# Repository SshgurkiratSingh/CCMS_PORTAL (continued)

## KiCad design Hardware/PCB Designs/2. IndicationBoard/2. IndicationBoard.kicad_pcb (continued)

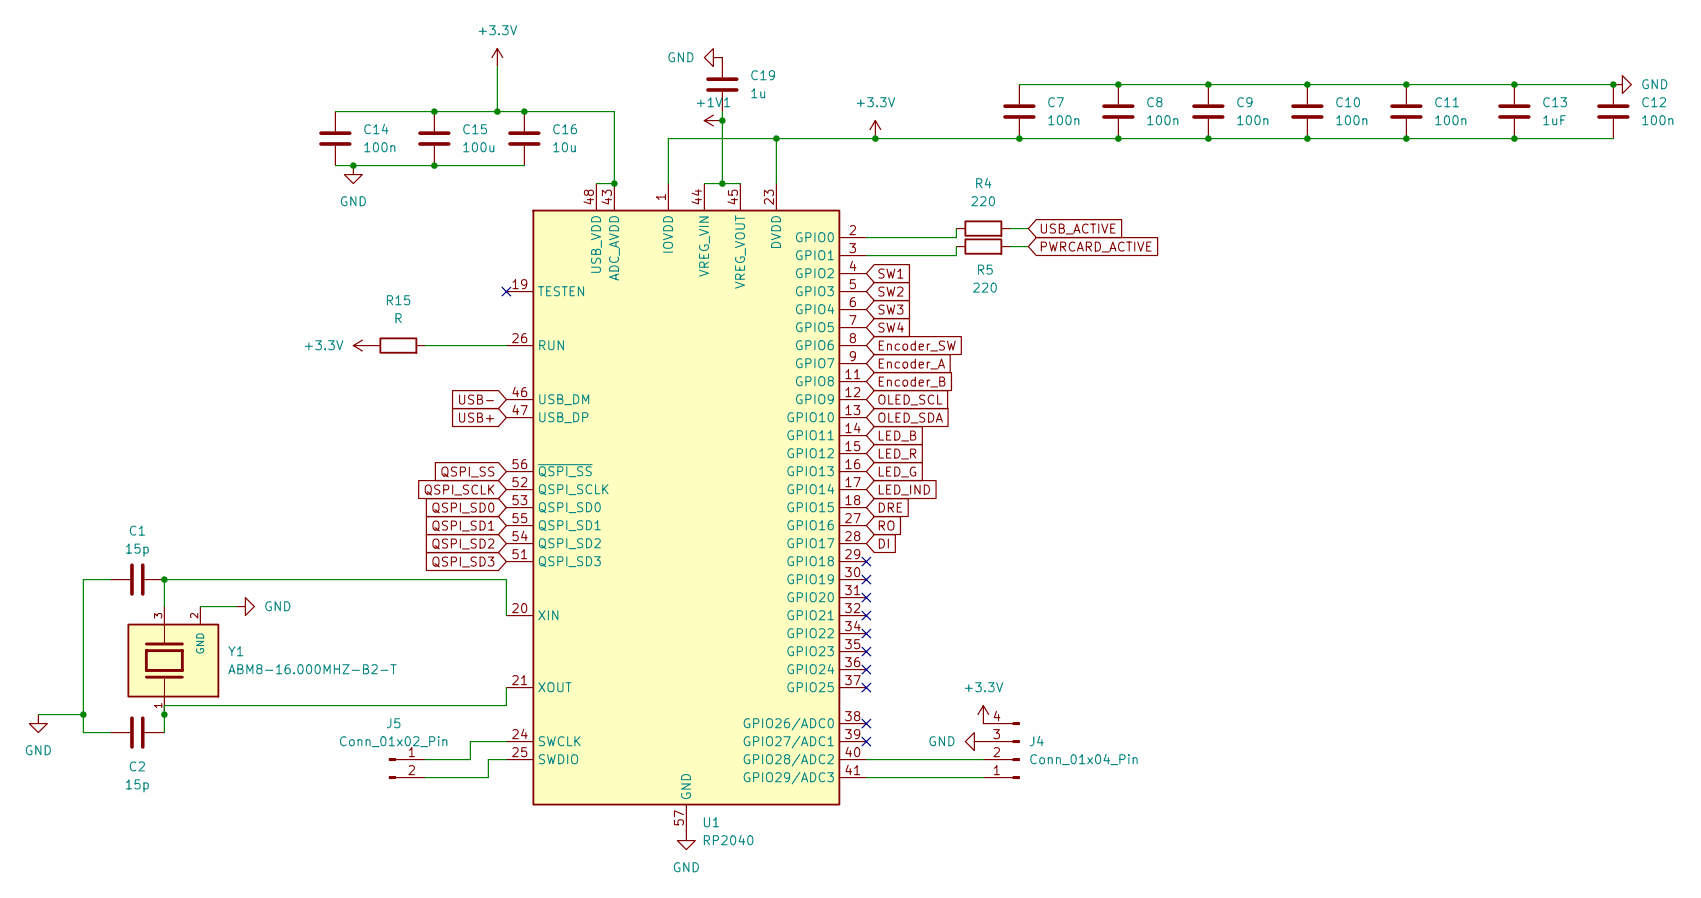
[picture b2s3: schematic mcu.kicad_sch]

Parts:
C1, C2: 15p; C_0402_1005Metric
C7, C8, C9, C10, C11, C12, C14: 100n; C_0201_0603Metric
C13: 1uF; C_0201_0603Metric
C15: 100u; C_0201_0603Metric
C16: 10u; C_0201_0603Metric
C19: 1u; C_0201_0603Metric
J4: Conn_01x04_Pin; PinSocket_1x04_P1.00mm_Vertical
J5: Conn_01x02_Pin; PinSocket_1x02_P2.00mm_Vertical
R4, R5: 220; R_0402_1005Metric
R15: R; R_0201_0603Metric
U1: RP2040; QFN-56-1EP_7x7mm_P0.4mm_EP3.2x3.2mm
Y1: ABM8-16.000MHZ-B2-T; XTAL_ABM8-16.000MHZ-B2-T; PARTREV 44041

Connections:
+1V1: C19.2, U1.44 (VREG_VIN), U1.45 (VREG_VOUT); also elsewhere on the board
+3.3V: C7.2, C8.2, C9.2, C10.2, C11.2, C12.2, C13.2, C14.1, C15.1, C16.1, J4.4, R15.1, U1.1 (IOVDD), U1.10 (IOVDD), U1.22 (IOVDD), U1.23 (DVDD), U1.33 (IOVDD), U1.42 (IOVDD), U1.43 (ADC_AVDD), U1.48 (USB_VDD), U1.49 (IOVDD), U1.50 (DVDD); also elsewhere on the board
DI: U1.28 (GPIO17); also elsewhere on the board
DRE: U1.18 (GPIO15); also elsewhere on the board
Encoder_A: U1.9 (GPIO7); also elsewhere on the board
Encoder_B: U1.11 (GPIO8); also elsewhere on the board
Encoder_SW: U1.8 (GPIO6); also elsewhere on the board
GND: C1.1, C2.1, C7.1, C8.1, C9.1, C10.1, C11.1, C12.1, C13.1, C14.2, C15.2, C16.2, C19.1, J4.3, U1.57 (GND), Y1.2 (GND), Y1.4 (GND); also elsewhere on the board
LED_B: U1.14 (GPIO11); also elsewhere on the board
LED_G: U1.16 (GPIO13); also elsewhere on the board
LED_IND: U1.17 (GPIO14); also elsewhere on the board
LED_R: U1.15 (GPIO12); also elsewhere on the board
unnamed: J4.1, U1.41 (GPIO29/ADC3)
unnamed: J4.2, U1.40 (GPIO28/ADC2)
unnamed: J5.1, U1.24 (SWCLK)
unnamed: J5.2, U1.25 (SWDIO)
unnamed: R4.1, U1.2 (GPIO0)
unnamed: R5.1, U1.3 (GPIO1)
unnamed: R15.2, U1.26 (RUN)
unnamed: C1.2, U1.20 (XIN), Y1.3
unnamed: C2.2, U1.21 (XOUT), Y1.1
OLED_SCL: U1.12 (GPIO9); also elsewhere on the board
OLED_SDA: U1.13 (GPIO10); also elsewhere on the board
PWRCARD_ACTIVE: R5.2; also elsewhere on the board
QSPI_SCLK: U1.52 (QSPI_SCLK); also elsewhere on the board
QSPI_SD0: U1.53 (QSPI_SD0); also elsewhere on the board
QSPI_SD1: U1.55 (QSPI_SD1); also elsewhere on the board
QSPI_SD2: U1.54 (QSPI_SD2); also elsewhere on the board
QSPI_SD3: U1.51 (QSPI_SD3); also elsewhere on the board
QSPI_SS: U1.56 (~QSPI_SS); also elsewhere on the board
RO: U1.27 (GPIO16); also elsewhere on the board
SW1: U1.4 (GPIO2); also elsewhere on the board
SW2: U1.5 (GPIO3); also elsewhere on the board
SW3: U1.6 (GPIO4); also elsewhere on the board
SW4: U1.7 (GPIO5); also elsewhere on the board
USB+: U1.47 (USB_DP); also elsewhere on the board
USB-: U1.46 (USB_DM); also elsewhere on the board
USB_ACTIVE: R4.2; also elsewhere on the board

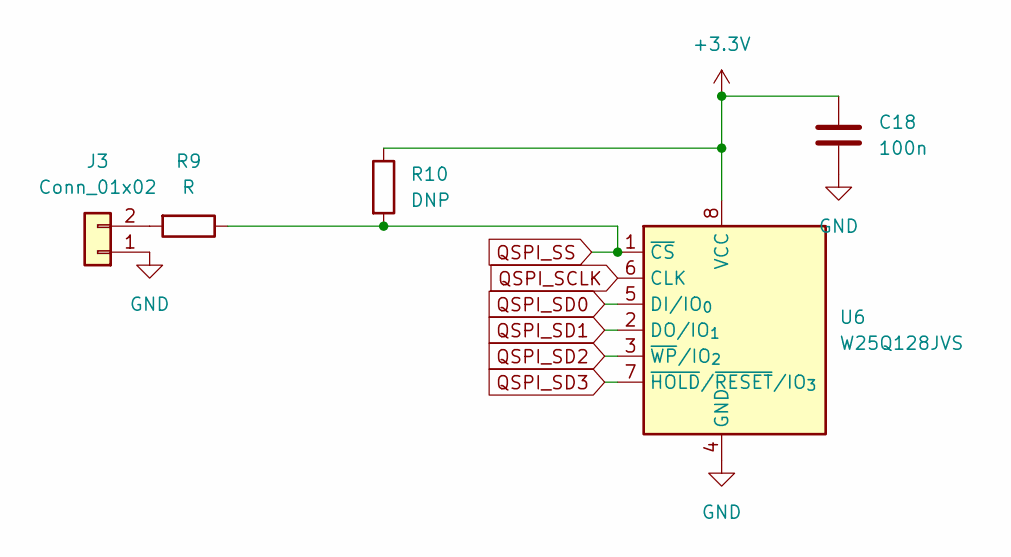
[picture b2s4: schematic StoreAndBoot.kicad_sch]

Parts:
C18: 100n; C_0402_1005Metric
J3: Conn_01x02; PinHeader_1x02_P1.00mm_Vertical
R9: R; R_0402_1005Metric
R10: DNP; R_0805_2012Metric
U6: W25Q128JVS; SOIC-8_5.3x5.3mm_P1.27mm

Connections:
+3.3V: C18.1, R10.1, U6.8 (VCC); also elsewhere on the board
GND: C18.2, J3.1, U6.4 (GND); also elsewhere on the board
unnamed: J3.2, R9.2
QSPI_SCLK: U6.6 (CLK); also elsewhere on the board
QSPI_SD0: U6.5 (DI/IO_{0}); also elsewhere on the board
QSPI_SD1: U6.2 (DO/IO_{1}); also elsewhere on the board
QSPI_SD2: U6.3 (~WP/IO_{2}); also elsewhere on the board
QSPI_SD3: U6.7 (~HOLD/~RESET/IO_{3}); also elsewhere on the board
QSPI_SS: R9.1, R10.2, U6.1 (~CS); also elsewhere on the board

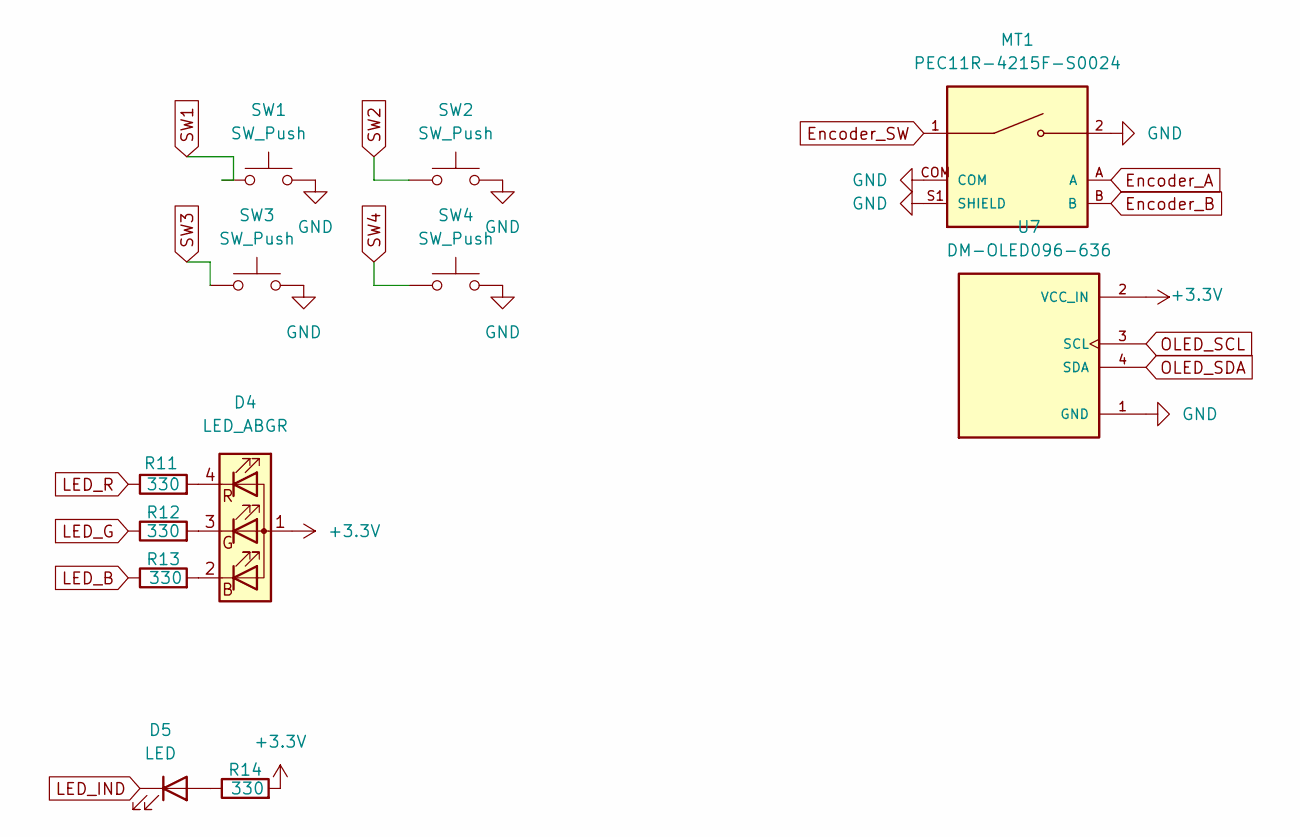
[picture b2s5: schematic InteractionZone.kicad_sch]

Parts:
D4: LED_ABGR; LED_RGB_Wuerth-PLCC4_3.2x2.8mm_150141M173100
D5: LED; LED_0805_2012Metric
MT1: PEC11R-4215F-S0024; XDCR_PEC11R-4215F-S0024; PARTREV Rev. 09/19
R11, R12, R13, R14: 330; R_0201_0603Metric
SW1, SW2, SW3, SW4: SW_Push; SW_PUSH_6mm_H8mm
U7: DM-OLED096-636; MODULE_DM-OLED096-636; PARTREV 2018-09-10

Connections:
+3.3V: D4.1 (A), R14.2, U7.2 (VCC_IN); also elsewhere on the board
Encoder_A: MT1.A; also elsewhere on the board
Encoder_B: MT1.B; also elsewhere on the board
Encoder_SW: MT1.1; also elsewhere on the board
GND: MT1.2, MT1.COM, MT1.S1 (SHIELD), MT1.S2 (SHIELD), SW1.2, SW2.2, SW3.2, SW4.2, U7.1 (GND); also elsewhere on the board
LED_B: R13.1; also elsewhere on the board
LED_G: R12.1; also elsewhere on the board
LED_IND: D5.1 (K); also elsewhere on the board
LED_R: R11.1; also elsewhere on the board
unnamed: D4.2 (BK), R13.2
unnamed: D4.3 (GK), R12.2
unnamed: D4.4 (RK), R11.2
unnamed: D5.2 (A), R14.1
OLED_SCL: U7.3 (SCL); also elsewhere on the board
OLED_SDA: U7.4 (SDA); also elsewhere on the board
SW1: SW1.1; also elsewhere on the board
SW2: SW2.1; also elsewhere on the board
SW3: SW3.1; also elsewhere on the board
SW4: SW4.1; also elsewhere on the board

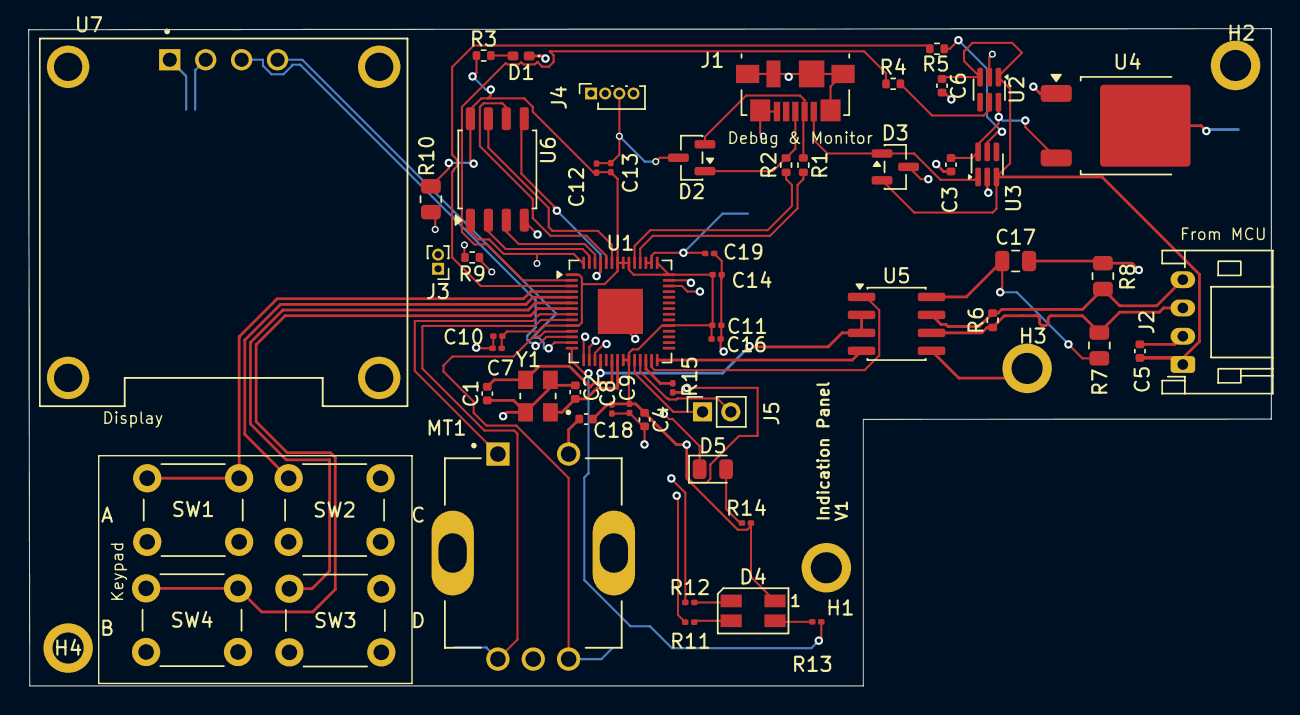
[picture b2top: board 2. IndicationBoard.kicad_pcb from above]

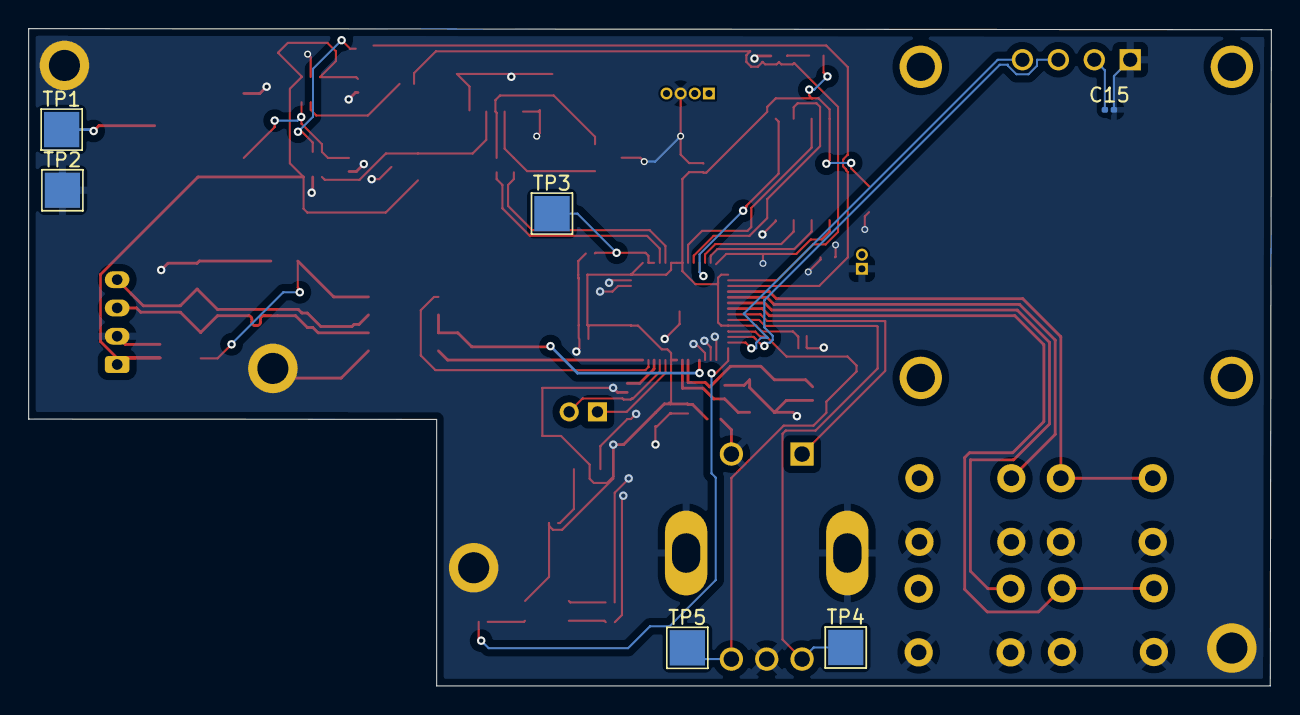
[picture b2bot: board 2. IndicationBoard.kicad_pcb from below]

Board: 4 copper layers, 87.9 x 46.5 mm, 66 parts (6 on the bottom side), 52 nets.

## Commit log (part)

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2026-02-23 content
2026-03-01 Bump minimatch in /ccms
    Bumps and [minimatch](https://github.com/isaacs/minimatch). These dependencies needed to be updated together.
    Updates `minimatch` from 3.1.3 to 3.1.5
    - [Changelog](https://github.com/isaacs/minimatch/blob/main/changelog.md)
    - [Commits](https://github.com/isaacs/minimatch/compare/v3.1.3...v3.1.5)
    Updates `minimatch` from 9.0.6 to 9.0.9
    - [Changelog](https://github.com/isaacs/minimatch/blob/main/changelog.md)
2026-03-20 feat:No-Shadow_implementation
2026-03-20 build(deps-dev): bump flatted from 3.3.3 to 3.4.2 in /ccms
    Bumps [flatted](https://github.com/WebReflection/flatted) from 3.3.3 to 3.4.2.
    - [Commits](https://github.com/WebReflection/flatted/compare/v3.3.3...v3.4.2)
    ---
    updated-dependencies:
    - dependency-name: flatted
    dependency-version: 3.4.2
2026-03-25 add:lambda
2026-03-26 build(deps): bump picomatch in /ccms
    Bumps and [picomatch](https://github.com/micromatch/picomatch). These dependencies needed to be updated together.
    Updates `picomatch` from 2.3.1 to 2.3.2
    - [Release notes](https://github.com/micromatch/picomatch/releases)
    - [Changelog](https://github.com/micromatch/picomatch/blob/master/CHANGELOG.md)
    - [Commits](https://github.com/micromatch/picomatch/compare/2.3.1...2.3.2)
    Updates `picomatch` from 4.0.3 to 4.0.4
2026-03-29 feat:added-map
2026-03-29 Bump next from 16.1.6 to 16.1.7 in /ccms
    Bumps [next](https://github.com/vercel/next.js) from 16.1.6 to 16.1.7.
    - [Release notes](https://github.com/vercel/next.js/releases)
    - [Changelog](https://github.com/vercel/next.js/blob/canary/release.js)
    - [Commits](https://github.com/vercel/next.js/compare/v16.1.6...v16.1.7)
    ---
    updated-dependencies:
2026-03-30 feat:added-map-registwermapping
2026-04-05 fix:adminaccess&feat:heroui change
2026-04-05 Deployed dea2c07 with MkDocs version: 1.6.1
2026-04-06 feat:relay-logic
2026-04-11 build(deps): bump next from 16.1.6 to 16.2.3 in /ccms
    Bumps [next](https://github.com/vercel/next.js) from 16.1.6 to 16.2.3.
    - [Release notes](https://github.com/vercel/next.js/releases)
    - [Changelog](https://github.com/vercel/next.js/blob/canary/release.js)
    - [Commits](https://github.com/vercel/next.js/compare/v16.1.6...v16.2.3)
    ---
    updated-dependencies:
2026-05-07 build(deps): bump brace-expansion in /ccms
    Bumps and [brace-expansion](https://github.com/juliangruber/brace-expansion). These dependencies needed to be updated together.
    Updates `brace-expansion` from 1.1.12 to 1.1.14
    - [Release notes](https://github.com/juliangruber/brace-expansion/releases)
    - [Commits](https://github.com/juliangruber/brace-expansion/compare/v1.1.12...v1.1.14)
    Updates `brace-expansion` from 5.0.3 to 5.0.5
    - [Release notes](https://github.com/juliangruber/brace-expansion/releases)
2026-05-07 update:ccms-code
2026-05-09 feat:chart
2026-05-09 fix:type
2026-05-10 feat:fix-relay
2026-05-12 build(deps): bump next from 16.1.6 to 16.2.6 in /ccms
    Bumps [next](https://github.com/vercel/next.js) from 16.1.6 to 16.2.6.
    - [Release notes](https://github.com/vercel/next.js/releases)
    - [Changelog](https://github.com/vercel/next.js/blob/canary/release.js)
    - [Commits](https://github.com/vercel/next.js/compare/v16.1.6...v16.2.6)
    ---
    updated-dependencies:
2026-05-18 build(deps-dev): bump brace-expansion from 5.0.3 to 5.0.6 in /ccms
    Bumps [brace-expansion](https://github.com/juliangruber/brace-expansion) from 5.0.3 to 5.0.6.
    - [Release notes](https://github.com/juliangruber/brace-expansion/releases)
    - [Commits](https://github.com/juliangruber/brace-expansion/compare/v5.0.3...v5.0.6)
    ---
    updated-dependencies:
    - dependency-name: brace-expansion
2026-06-19 fix:readme
2026-06-19 build(deps-dev): bump js-yaml from 4.1.1 to 4.2.0 in /ccms
    Bumps [js-yaml](https://github.com/nodeca/js-yaml) from 4.1.1 to 4.2.0.
    - [Changelog](https://github.com/nodeca/js-yaml/blob/master/CHANGELOG.md)
    - [Commits](https://github.com/nodeca/js-yaml/commits)
    ---
    updated-dependencies:
    - dependency-name: js-yaml
